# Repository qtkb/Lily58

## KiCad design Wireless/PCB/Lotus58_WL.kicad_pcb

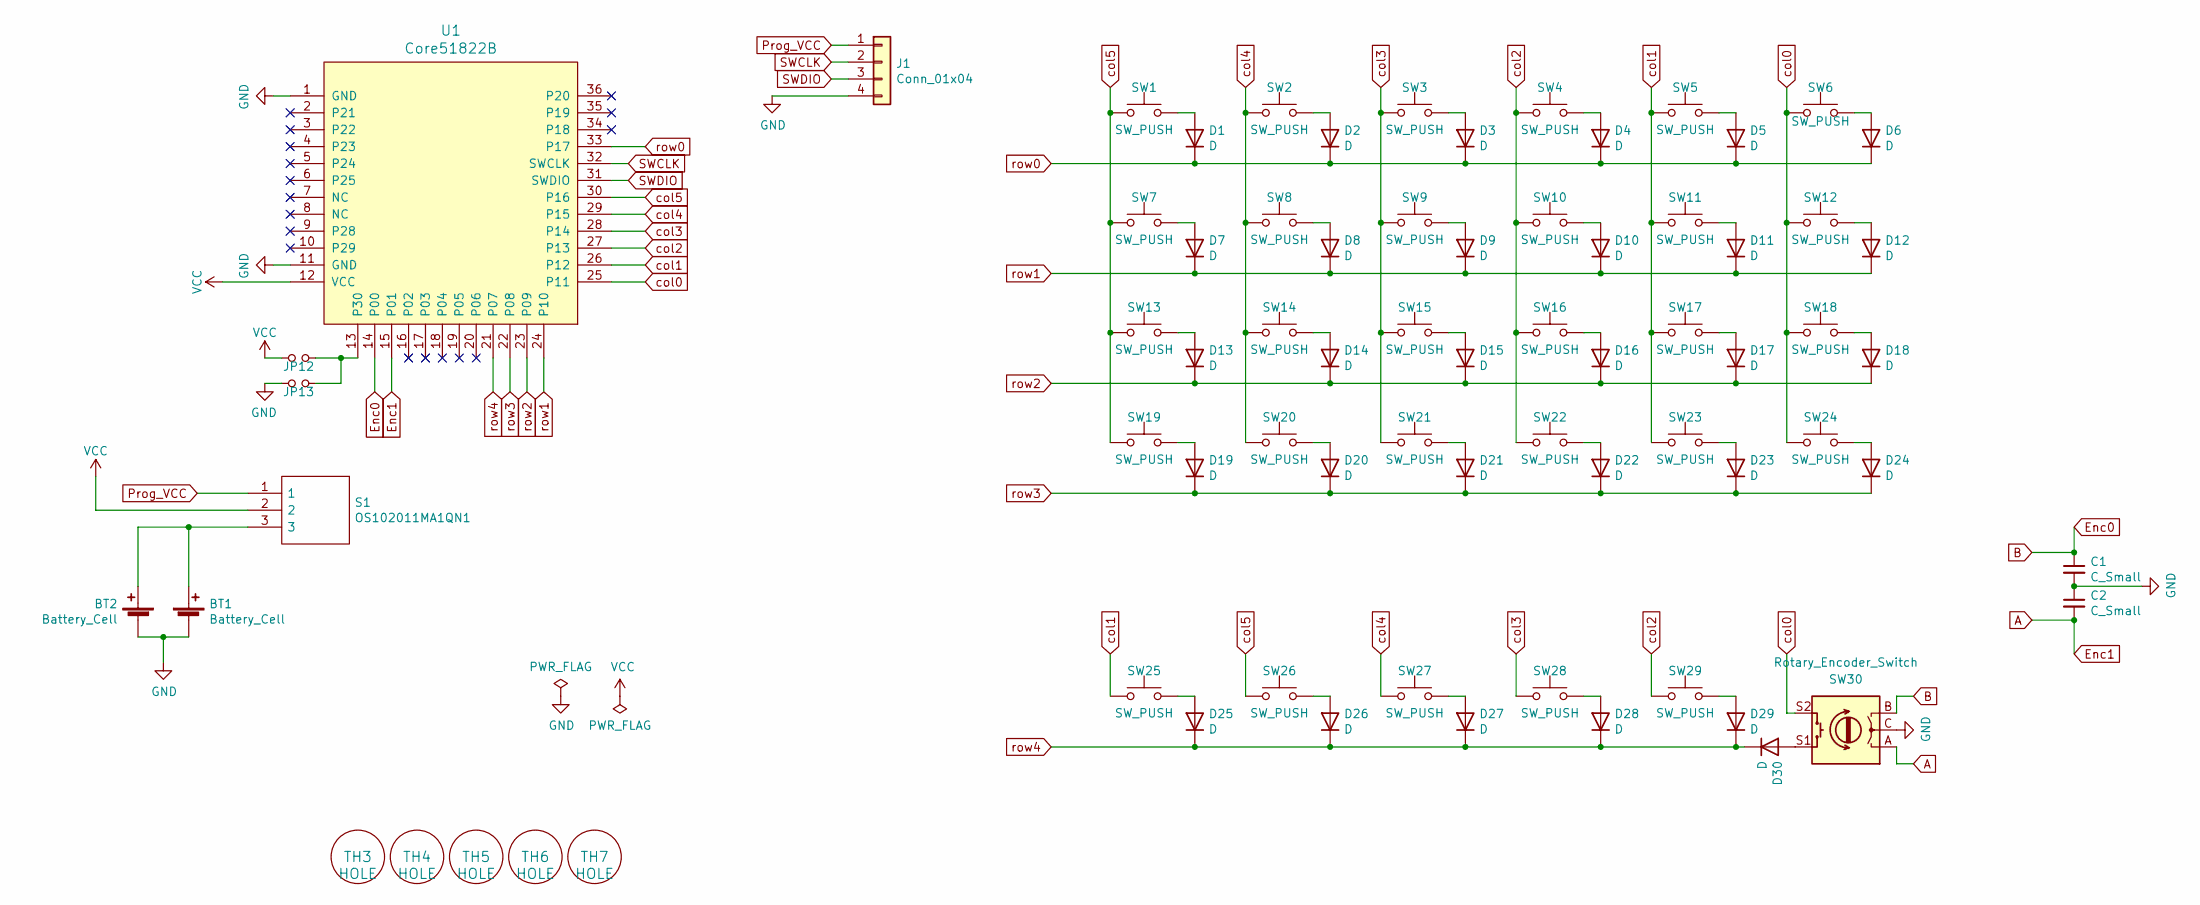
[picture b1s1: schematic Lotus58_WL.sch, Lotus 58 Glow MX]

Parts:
BT1, BT2: Battery_Cell; BAT_BK-888
C1, C2: C_Small; RESISTOR_Reversible
D1, D2, D3, D4, D5, D6, D7, D8, D9, D10, D11, D12, D13, D14, D15, D16, D17, D18, D19, D20, D21, D22, D23, D24, D25, D26, D27, D28, D29, D30: D; Diode_DO35_SOD123
J1: Conn_01x04; PinHeader_1x04_P2.54mm_Vertical
JP12: LH; Jumper_Mini
JP13: RH; Jumper_Mini
S1: OS102011MA1QN1; Mouser Part Number 611-OS102011MA1QN1
SW1, SW2, SW3, SW4, SW5, SW6, SW7, SW8, SW9, SW10, SW11, SW12, SW13, SW14, SW15, SW16, SW17, SW18, SW19, SW20, SW21, SW22, SW23, SW24, SW25, SW26, SW27, SW28, SW29: SW_PUSH; Kaih_socket_MX_Choc_V1&V2_reversible
SW30: Rotary_Encoder_Switch; RotaryEncoder_EC11-no-legs
TH3, TH4, TH5, TH6, TH7: HOLE; MountingHole_2.7mm_M2.5
U1: Core51822B; Core51822(B)

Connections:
A: C2.2, SW30.A, U1.15 (P01)
B: C1.1, SW30.B, U1.14 (P00)
GND: BT1.2 (-), BT2.2 (-), C1.2, C2.1, J1.4, JP13.2, SW30.C, U1.1 (GND), U1.11 (GND); also elsewhere on the board
unnamed: BT1.1 (+), BT2.1 (+), S1.3
unnamed: D1.2 (A), SW1.2
unnamed: D2.2 (A), SW2.2
unnamed: D3.2 (A), SW3.2
unnamed: D4.2 (A), SW4.2
unnamed: D5.2 (A), SW5.2
unnamed: D6.2 (A), SW6.2
unnamed: D7.2 (A), SW7.2
unnamed: D8.2 (A), SW8.2
unnamed: D9.2 (A), SW9.2
unnamed: D10.2 (A), SW10.2
unnamed: D11.2 (A), SW11.2
unnamed: D12.2 (A), SW12.2
unnamed: D13.2 (A), SW13.2
unnamed: D14.2 (A), SW14.2
unnamed: D15.2 (A), SW15.2
unnamed: D16.2 (A), SW16.2
unnamed: D17.2 (A), SW17.2
unnamed: D18.2 (A), SW18.2
unnamed: D19.2 (A), SW19.2
unnamed: D20.2 (A), SW20.2
unnamed: D21.2 (A), SW21.2
unnamed: D22.2 (A), SW22.2
unnamed: D23.2 (A), SW23.2
unnamed: D24.2 (A), SW24.2
unnamed: D25.2 (A), SW25.2
unnamed: D26.2 (A), SW26.2
unnamed: D27.2 (A), SW27.2
unnamed: D28.2 (A), SW28.2
unnamed: D29.2 (A), SW29.2
unnamed: D30.2 (A), SW30.S1
unnamed: JP12.1, JP13.1, U1.13 (P30)
Prog_VCC: J1.1, S1.1; also elsewhere on the board
SWCLK: J1.2, U1.32 (SWCLK); also elsewhere on the board
SWDIO: J1.3, U1.31 (SWDIO); also elsewhere on the board
VCC: JP12.2, S1.2, U1.12 (VCC)
col0: SW6.1, SW12.1, SW18.1, SW24.1, SW30.S2, U1.25 (P11)
col1: SW5.1, SW11.1, SW17.1, SW23.1, SW25.1, U1.26 (P12)
col2: SW4.1, SW10.1, SW16.1, SW22.1, SW29.1, U1.27 (P13)
col3: SW3.1, SW9.1, SW15.1, SW21.1, SW28.1, U1.28 (P14)
col4: SW2.1, SW8.1, SW14.1, SW20.1, SW27.1, U1.29 (P15)
col5: SW1.1, SW7.1, SW13.1, SW19.1, SW26.1, U1.30 (P16)
row0: D1.1 (K), D2.1 (K), D3.1 (K), D4.1 (K), D5.1 (K), D6.1 (K), U1.33 (P17)
row1: D7.1 (K), D8.1 (K), D9.1 (K), D10.1 (K), D11.1 (K), D12.1 (K), U1.24 (P10)
row2: D13.1 (K), D14.1 (K), D15.1 (K), D16.1 (K), D17.1 (K), D18.1 (K), U1.23 (P09)
row3: D19.1 (K), D20.1 (K), D21.1 (K), D22.1 (K), D23.1 (K), D24.1 (K), U1.22 (P08)
row4: D25.1 (K), D26.1 (K), D27.1 (K), D28.1 (K), D29.1 (K), D30.1 (K), U1.21 (P07)

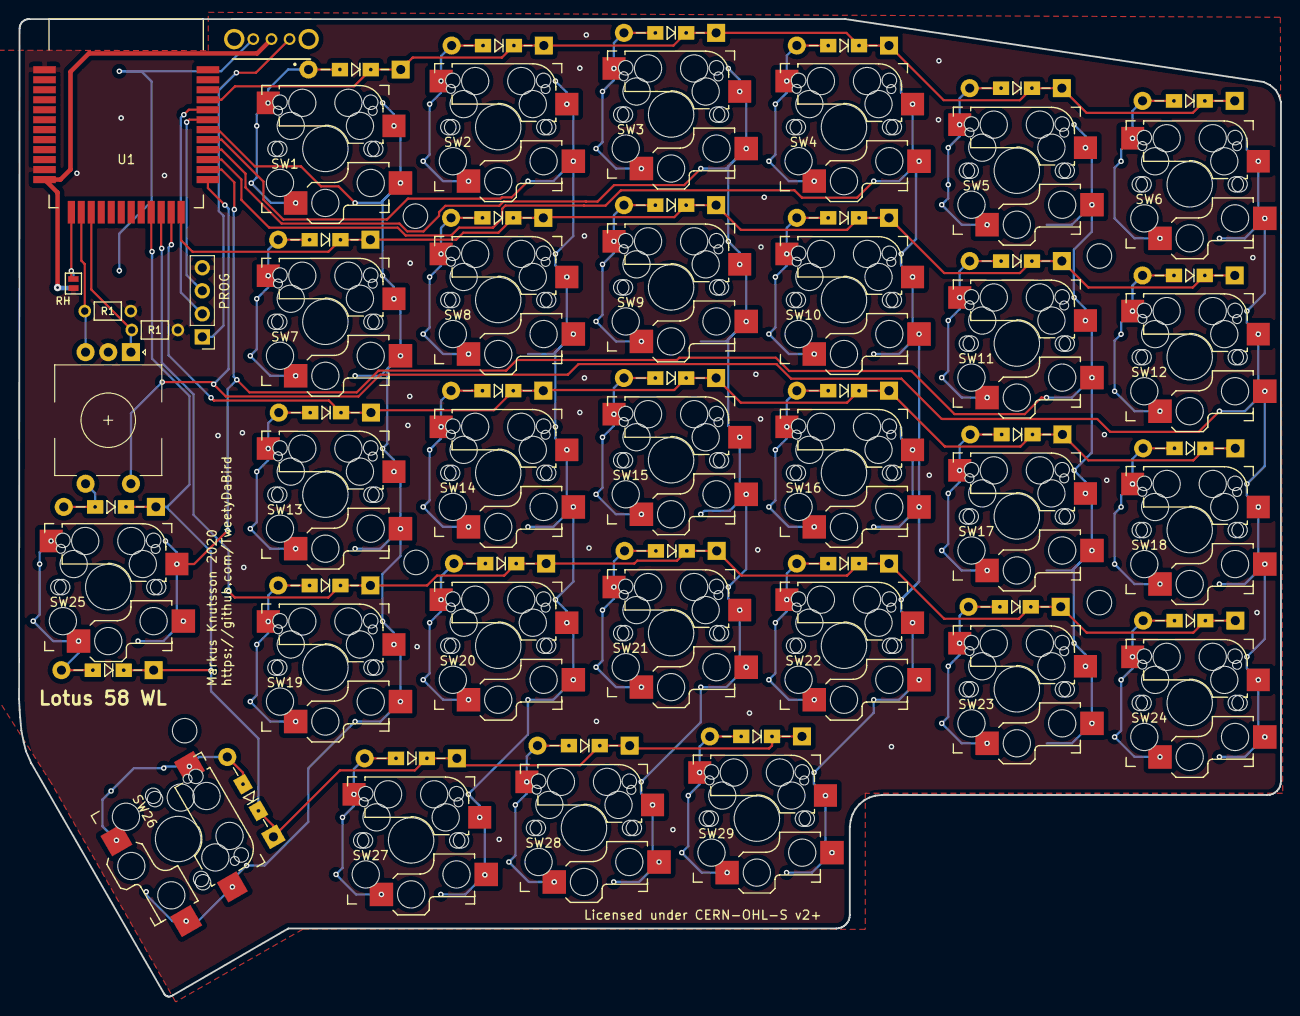
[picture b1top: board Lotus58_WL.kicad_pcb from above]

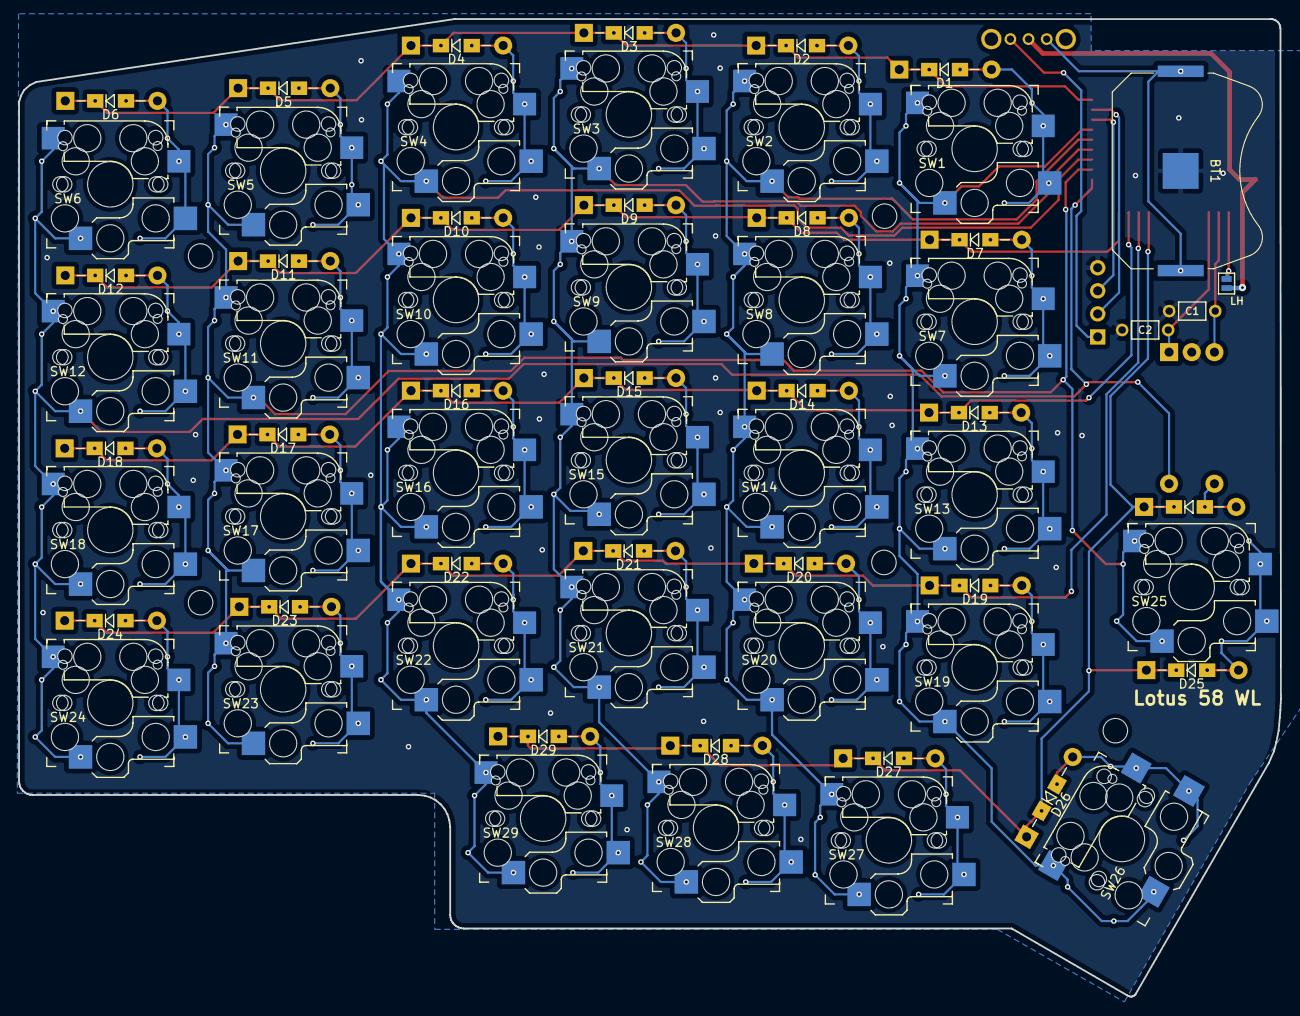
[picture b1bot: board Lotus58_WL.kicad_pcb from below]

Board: 2 copper layers, 139.1 x 107.7 mm, 73 parts (33 on the bottom side), 50 nets.

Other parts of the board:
PROG: Conn_01x04; PinHeader_1x04_P2.54mm_Vertical

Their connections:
GND: PROG.4; also elsewhere on the board
Prog_VCC: PROG.1; also elsewhere on the board
SWCLK: PROG.2; also elsewhere on the board
SWDIO: PROG.3; also elsewhere on the board

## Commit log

2020-01-23 Uodate VCC connection on underglow LED
2020-09-26 Update VCC connection on underglow LED
2021-01-27 Initial commit Wireless

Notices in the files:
Wireless/PCB/Lotus58_WL.kicad_pcb:
Licensed under CERN-OHL-S v2 or any superseding version
